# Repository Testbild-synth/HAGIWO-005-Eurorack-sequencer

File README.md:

# HAGIWO 005 Eurorack Generative Sequencer Module

Through hole PCB version of the [HAGIWO 005 Generative Sequencer](https://www.youtube.com/watch?v=S4yxVxi9Iak) Eurorack module.
The module is a very simple Arduino-based CV and gate generator that gives random sequences similar to a music things modular turing machine.
Parameters can be set to change different parameters of the sequence.

## Hardware and PCB

You can find the schematic and BOM in the root folder. For the PCBs, the module has one circuit PCB and one panel PCB. You can order them on any common PCB manufacturing service, I used JLCPCB. Standard settings should be fine.

I have uploaded the panel kicad and inkscape files if you want to change fonts etc. (I use the great [svg2shenzen](https://github.com/badgeek/svg2shenzhen) inkscape extension to do my panels.

you should probably make the led resistors (the 330 ohm ones) something higher like 1k, the leds on mine are very bright

As with some of my other modules, this pcb has a selector which allows you to choose if it runs off the 12V or 5V power bus (as some people want 5V but others don't have it in their racks). simply solder the bridge from V_sel to either side or put in a jumper to choose.    

# TODO:
- code cleanup (it works but could be prettier)

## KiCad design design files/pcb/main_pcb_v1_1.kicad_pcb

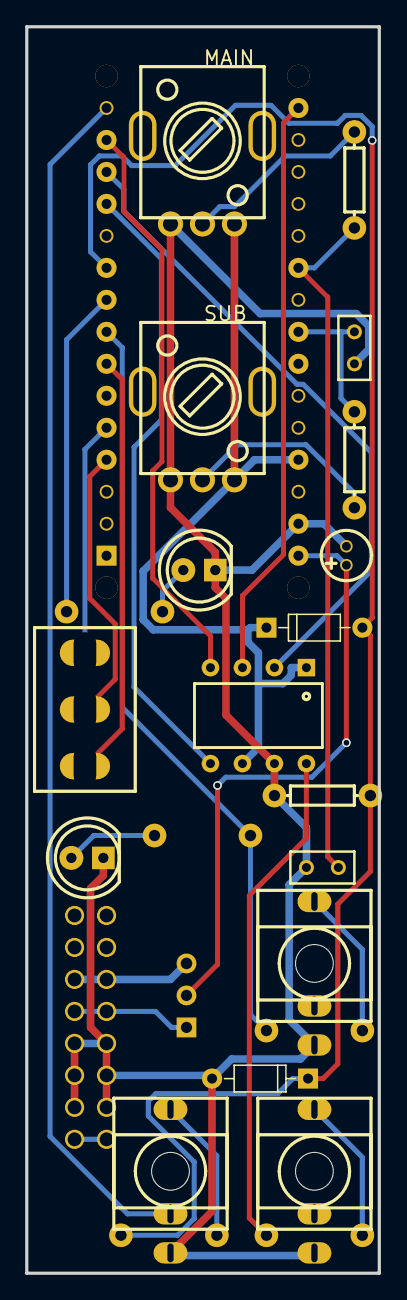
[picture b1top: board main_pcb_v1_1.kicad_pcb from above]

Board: 2 copper layers, 28.0 x 99.0 mm, 25 parts (0 on the bottom side), 27 nets.

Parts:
5V: HDR-F-2.54_1x3; HDR-F-2.54_1X3
C1: 10u; CAP-D4.0×F1.5
C2, C3: 220p; RAD-0.1
D1, D2: BAT43; D_DO-35_SOD27_P7.62MM_HORIZONTAL
J3: CLOCK_IN; THONKICONN_1
J4: GATE_OUT; THONKICONN_1
J11: V_OUT; THONKICONN_1
LED1: GATE_LED; LED 5MM
LED2: OUT_LED; LED 5MM
MAIN: 100k; R09-5KΩ
P18: PWR; HDR-IDC-2.54-2X8P
R1, R3, R11: 470; R_AXIAL-0.3
R2, R4: 1k; R_AXIAL-0.3
R5, R6: 2.2k; R_AXIAL-0.3
R7: 100k; R_AXIAL-0.3
SUB: 100k; R09-5KΩ
U1: ARDUINO_NANO; ARDUINO_NANO_WITHMOUNTINGHOLES
U2: MCP4911-EP; DIP8
U3: Switch; SWITCH

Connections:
5V: 5V.3, P18.11, P18.12
12V: 5V.1, P18.9, P18.10
-12V: P18.1, P18.2
ARD_5: D1.1, MAIN.3, SUB.3, U1.27, U2.1, U2.6
GND: C1.2, C2.1, C3.1, D2.2, J3.1, J4.1, J11.1, LED1.2, LED2.2, MAIN.1, P18.3, P18.4, P18.5, P18.6, P18.7, P18.8, R7.2, SUB.1, U1.29, U2.7
J3_3: J3.3, R3.2
J4_3: J4.3, R4.1
MAIN_2: MAIN.2, R11.2
R2_1: J11.3, R2.1
R5_2: LED1.1, R5.2
R6_2: LED2.1, R6.2
SUB_2: R1.2, SUB.2
U1_4: U1.4, U3.5
U1_5: U1.5, U3.4
U1_7: U1.7, U3.6
U1_8: R4.2, R5.1, U1.8
U1_9: R6.1, U1.9
U1_10: D1.2, D2.1, R3.1, R7.1, U1.10
U1_12: U1.12, U2.5
U1_13: U1.13, U2.2
U1_14: U1.14, U2.4
U1_15: J3.2, U1.15
U1_16: U1.16, U2.3
U1_21: C2.2, R11.1, U1.21
U1_23: C3.2, R1.1, U1.23
U1_30: 5V.2, C1.1, U1.30
U2_8: R2.2, U2.8

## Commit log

2022-02-01 upload arduino code
2022-02-01 added panel pcb files and kicad
2022-02-01 Add files via upload
    added schematic and BOM
2022-02-02 fixed youtube link for hagiwos channel
2022-02-03 new folder structure to keep consistent with other repos
2022-02-03 upload kicad and easyeda files
2022-11-08 slight fixes and simplifications for main pcb
